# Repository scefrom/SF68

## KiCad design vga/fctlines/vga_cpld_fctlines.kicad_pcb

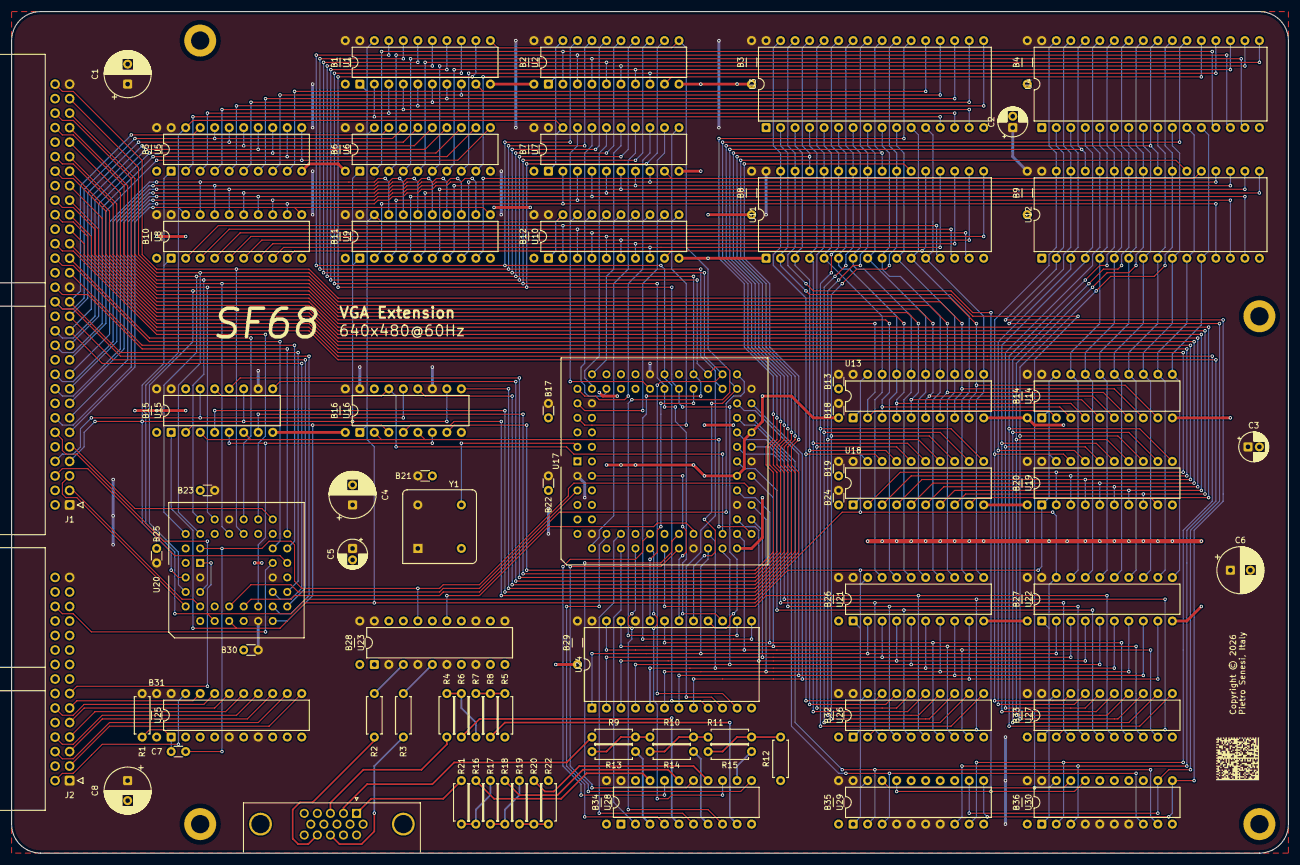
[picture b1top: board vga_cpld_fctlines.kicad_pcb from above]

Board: 2 copper layers, 223.5 x 147.3 mm, 104 parts (0 on the bottom side), 214 nets.

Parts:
B1, B2, B3, B4, B5, B6, B7, B8, B9, B10, B11, B12, B14, B15, B16, B20, B26, B27, B28, B29, B31, B32, B33, B34, B35, B36: 100n; C_Disc_D3.0mm_W1.6mm_P7.62mm
B13, B17, B18, B19, B21, B22, B23, B24, B25, B30: 100n; C_Disc_D3.0mm_W1.6mm_P2.54mm
C1, C4, C6, C8: 100u; CP_Radial_D8.0mm_P3.50mm
C2, C3, C5: 10u; CP_Radial_D5.0mm_P2.00mm
C7: 22p; C_Disc_D3.0mm_W1.6mm_P2.54mm
J1: perslota; IDC-Header_2x30_P2.54mm_Horizontal
J2: perslotb; IDC-Header_2x15_P2.54mm_Horizontal
J3: vga_connector; DSUB-15-HD_Socket_Horizontal_P2.29x1.90mm_EdgePinOffset3.03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
M1, M2, M3, M4: MountingHole_3.2mm_M3_DIN965_Pad
R1: 4.7k; R_Axial_DIN0207_L6.3mm_D2.5mm_P7.62mm_Horizontal
R2, R3: 75; R_Axial_DIN0207_L6.3mm_D2.5mm_P7.62mm_Horizontal
R4: 226; R_Axial_DIN0207_L6.3mm_D2.5mm_P7.62mm_Horizontal
R5, R6, R8, R12, R13, R14, R15, R16, R18, R20, R22: 200; R_Axial_DIN0207_L6.3mm_D2.5mm_P7.62mm_Horizontal
R7, R10, R11, R17, R19: 100; R_Axial_DIN0207_L6.3mm_D2.5mm_P7.62mm_Horizontal
R9, R21: 294; R_Axial_DIN0207_L6.3mm_D2.5mm_P7.62mm_Horizontal
U1, U2, U7, U10, U13, U14, U18, U19, U21, U22, U26, U27, U29, U30: 74AHC541; DIP-20_W7.62mm
U3, U4, U11, U12: AS6C4008-55PCN; DIP-32_W15.24mm
U5, U6, U8, U9: 74HC245; DIP-20_W7.62mm
U15, U16: 74HC157; DIP-16_W7.62mm
U17: ATF1508AS-xJx84; PLCC-84_THT-Socket
U20: ATF1502AS-xJx44; PLCC-44_THT-Socket
U23, U28: CY74FCT244; DIP-20_W7.62mm
U24: AT28C16; DIP-24_W15.24mm
U25: 74HC541; DIP-20_W7.62mm
Y1: CXO_DIP8_25.175MHz; Oscillator_DIP-8

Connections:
+5V: B1.1, B2.1, B3.1, B4.1, B5.1, B6.1, B7.1, B8.1, B9.1, B10.1, B11.1, B12.1, B13.1, B14.1, B15.1, B16.1, B17.1, B18.1, B19.1, B20.1, B21.1, B22.1, B23.1, B24.1, B25.1, B26.1, B27.1, B28.1, B29.1, B30.1, B31.1, B32.1, B33.1, B34.1, B35.1, B36.1, C1.1, C2.1, C3.1, C4.1, C5.1, C6.1, C8.1, J1.1, J1.31, J1.59, J2.1, J2.29, R1.1, U1.20 (VCC), U2.20 (VCC), U3.32 (VCC), U4.32 (VCC), U5.20 (VCC), U6.20 (VCC), U7.20 (VCC), U8.20 (VCC), U9.20 (VCC), U10.20 (VCC), U11.32 (VCC), U12.32 (VCC), U13.20 (VCC), U14.20 (VCC), U15.10 (I1c), U15.16 (VCC), U16.11 (I0c), U16.16 (VCC), U17.3 (VCC_INT), U17.13 (VCC_IO), U17.26 (VCC_IO), U17.38 (VCC_IO), U17.43 (VCC_INT), U17.53 (VCC_IO), U17.66 (VCC_IO), U17.78 (VCC_IO), U18.20 (VCC), U19.20 (VCC), U20.3 (VCC), U20.15 (VCC), U20.23 (VCC), U20.35 (VCC), U21.20 (VCC), U22.20 (VCC), U23.2, U23.4, U23.6, U23.8, U23.11, U23.13, U23.20 (VCC), U24.21 (~WE), U24.24 (VCC), U25.5 (A3), U25.7 (A5), U25.20 (VCC), U26.20 (VCC), U27.20 (VCC), U28.20 (VCC), U29.4 (A2), U29.5 (A3), U29.6 (A4), U29.7 (A5), U29.20 (VCC), U30.4 (A2), U30.5 (A3), U30.6 (A4), U30.7 (A5), U30.20 (VCC), Y1.1 (EN), Y1.8 (Vcc)
/AC.~P: J2.26, U20.25 (I/O/PD2)
/ADR_{0}: U17.51 (I/O), U21.9 (A7), U22.9 (A7), U24.8 (A0)
/ADR_{1}: U17.52 (I/O), U21.8 (A6), U22.8 (A6), U24.7 (A1)
/ADR_{2}: U17.37 (I/O), U21.7 (A5), U22.7 (A5), U24.6 (A2)
/ADR_{3}: U17.29 (I/O), U21.6 (A4), U22.6 (A4), U24.5 (A3)
/ADR_{4}: U17.30 (I/O), U21.5 (A3), U22.5 (A3), U24.4 (A4)
/ADR_{5}: U17.36 (I/O), U21.4 (A2), U22.4 (A2), U24.3 (A5)
/ADR_{6}: U17.35 (I/O), U21.3 (A1), U22.3 (A1), U24.2 (A6)
/ADR_{7}: U17.28 (I/O), U21.2 (A0), U22.2 (A0), U24.1 (A7)
/ADR_{8}: U17.34 (I/O), U24.23 (A8), U26.9 (A7), U27.9 (A7)
/ADR_{9}: U17.41 (I/O), U24.22 (A9), U26.8 (A6), U27.8 (A6)
/ADR_{10}: U17.40 (I/O), U24.19 (A10), U26.7 (A5), U27.7 (A5)
/ADR_{11}: U17.22 (I/O), U26.6 (A4), U27.6 (A4)
/ADR_{12}: U17.44 (I/O), U26.5 (A3), U27.5 (A3)
/ADR_{13}: U17.48 (I/O), U26.4 (A2), U27.4 (A2)
/ADR_{14}: U17.46 (I/O), U26.3 (A1), U27.3 (A1)
/ADR_{15}: U17.45 (I/O/PD2), U26.2 (A0), U27.2 (A0)
/ADR_{16}: U17.49 (I/O), U29.2 (A0), U30.9 (A7)
/ADR_{17}: U17.50 (I/O), U29.3 (A1), U30.8 (A6)
/A_{1}: J1.60, U13.9 (A7), U14.9 (A7), U20.34 (I/O)
/A_{2}: J1.57, U13.8 (A6), U14.8 (A6), U20.41 (I/O/GCLK3)
/A_{3}: J1.55, U13.7 (A5), U14.7 (A5), U20.40 (I/O)
/A_{4}: J1.56, U13.6 (A4), U14.6 (A4), U20.39 (I/O)
/A_{5}: J1.53, U13.5 (A3), U14.5 (A3), U20.36 (I/O)
/A_{6}: J1.54, U13.4 (A2), U14.4 (A2), U20.37 (I/O)
/A_{7}: J1.51, U13.3 (A1), U14.3 (A1), U20.4 (I/O)
/A_{8}: J1.49, U13.2 (A0), U14.2 (A0)
/A_{9}: J1.50, U18.9 (A7), U19.9 (A7)
/A_{10}: J1.47, U18.8 (A6), U19.8 (A6)
/A_{11}: J1.48, U18.7 (A5), U19.7 (A5)
/A_{12}: J1.45, U18.6 (A4), U19.6 (A4)
/A_{13}: J1.43, U18.5 (A3), U19.5 (A3)
/A_{14}: J1.44, U18.4 (A2), U19.4 (A2)
/A_{15}: J1.41, U18.3 (A1), U19.3 (A1)
/A_{16}: J1.42, U18.2 (A0), U19.2 (A0)
/A_{17}: J1.39, U29.9 (A7), U30.2 (A0)
/A_{18}: J1.37, U29.8 (A6), U30.3 (A1)
/A_{19}: J1.38, U20.31 (I/O)
/A_{20}: J1.35, U20.33 (I/O)
/A_{21}: J1.36, U20.27 (I/O)
/A_{22}: J1.33, U20.26 (I/O)
/A_{23}: J1.32, U20.28 (I/O)
/BE.~IO: J1.12, U20.5 (I/O)
/BE.~M: J1.9, U20.29 (I/O)
/CLK: U17.83 (I/GCLK1), Y1.5 (OUT)
/CM: U17.5 (I/O), U20.12 (I/O)
/DAT_{0}: U1.18 (Y0), U2.18 (Y0), U17.64 (I/O), U24.9 (D0)
/DAT_{1}: U1.17 (Y1), U2.17 (Y1), U17.57 (I/O), U24.10 (D1)
/DAT_{2}: U1.16 (Y2), U2.16 (Y2), U17.56 (I/O), U24.11 (D2)
/DAT_{3}: U1.15 (Y3), U2.15 (Y3), U17.60 (I/O), U24.13 (D3)
/DAT_{4}: U1.14 (Y4), U2.14 (Y4), U17.58 (I/O), U24.14 (D4)
/DAT_{5}: U1.13 (Y5), U2.13 (Y5), U17.65 (I/O), U24.15 (D5)
/DAT_{6}: U1.12 (Y6), U2.12 (Y6), U17.63 (I/O), U24.16 (D6)
/DAT_{7}: U1.11 (Y7), U2.11 (Y7), U17.55 (I/O), U24.17 (D7)
/DAT_{8}: U7.18 (Y0), U10.18 (Y0), U17.67 (I/O)
/DAT_{9}: U7.17 (Y1), U10.17 (Y1), U17.73 (I/O)
/DAT_{10}: U7.16 (Y2), U10.16 (Y2), U17.76 (I/O)
/DAT_{11}: U7.15 (Y3), U10.15 (Y3), U17.74 (I/O)
/DAT_{12}: U7.14 (Y4), U10.14 (Y4), U17.12 (I/O/PD1)
/DAT_{13}: U7.13 (Y5), U10.13 (Y5), U17.75 (I/O)
/DAT_{14}: U7.12 (Y6), U10.12 (Y6), U17.77 (I/O)
/DAT_{15}: U7.11 (Y7), U10.11 (Y7), U17.79 (I/O)
/DIR.~R: J1.8, U15.14 (I0d), U16.13 (I1d)
/DIR.~W: J1.7, U5.1 (A->B), U6.1 (A->B), U8.1 (A->B), U9.1 (A->B), U15.11 (I0c), U16.10 (I1c), U20.2 (I/GCLK2/OE2)
/DS.~L: J1.6, U20.24 (I/O)
/DS.~U: J1.5, U20.6 (I/O)
/D_{0}: J1.29, U5.18 (B0), U6.18 (B0), U20.20 (I/O)
/D_{1}: J1.30, U5.17 (B1), U6.17 (B1), U20.19 (I/O)
/D_{2}: J1.27, U5.16 (B2), U6.16 (B2), U20.18 (I/O)
/D_{3}: J1.25, U5.15 (B3), U6.15 (B3), U20.21 (I/O)
/D_{4}: J1.26, U5.14 (B4), U6.14 (B4)
/D_{5}: J1.23, U5.13 (B5), U6.13 (B5)
/D_{6}: J1.24, U5.12 (B6), U6.12 (B6)
/D_{7}: J1.21, U5.11 (B7), U6.11 (B7)
/D_{8}: J1.19, U8.18 (B0), U9.18 (B0)
/D_{9}: J1.20, U8.17 (B1), U9.17 (B1)
/D_{10}: J1.17, U8.16 (B2), U9.16 (B2)
/D_{11}: J1.18, U8.15 (B3), U9.15 (B3)
/D_{12}: J1.15, U8.14 (B4), U9.14 (B4)
/D_{13}: J1.13, U8.13 (B5), U9.13 (B5)
/D_{14}: J1.14, U8.12 (B6), U9.12 (B6)
/D_{15}: J1.11, U8.11 (B7), U9.11 (B7)
/IBSY: J2.2, U25.19 (G2)
/IRQ_{0}: J2.11, U25.18 (Y0)
/IRQ_{1}: J2.12, U25.17 (Y1)
/IRQ_{2}: J2.9, U25.16 (Y2)
/IRQ_{3}: J2.7, U25.15 (Y3)
/IRQ_{4}: J2.8, U25.14 (Y4)
/IRQ_{5}: J2.5, U25.13 (Y5)
/IRQ_{6}: J2.6, U25.12 (Y6)
/IRQ_{7}: J2.3, U25.11 (Y7)
/RGB_{0}: U17.25 (I/O), U28.15
/RGB_{1}: U17.24 (I/O), U28.11
/RGB_{2}: U17.21 (I/O), U28.17
/RGB_{3}: U17.20 (I/O/PD), U28.13
/RGB_{4}: U17.18 (I/O), U28.8
/RGB_{5}: U17.16 (I/O), U28.2
/RGB_{6}: U17.15 (I/O), U28.4
/RGB_{7}: U17.17 (I/O), U28.6
/UP: U17.54 (I/O), U20.14 (I/O)
/VBS: U1.1 (G1), U1.19 (G2), U6.19 (CE), U9.19 (CE), U10.1 (G1), U10.19 (G2), U14.1 (G1), U14.19 (G2), U15.1 (S), U16.1 (S), U19.1 (G1), U19.19 (G2), U20.11 (I/O/PD1), U21.1 (G1), U21.19 (G2), U26.1 (G1), U26.19 (G2), U29.1 (G1), U29.19 (G2)
/VB_{0}A_{0}: U3.12 (A0), U11.12 (A0), U13.11 (Y7), U21.11 (Y7)
/VB_{0}A_{1}: U3.11 (A1), U11.11 (A1), U13.12 (Y6), U21.12 (Y6)
/VB_{0}A_{2}: U3.10 (A2), U11.10 (A2), U13.13 (Y5), U21.13 (Y5)
/VB_{0}A_{3}: U3.9 (A3), U11.9 (A3), U13.14 (Y4), U21.14 (Y4)
/VB_{0}A_{4}: U3.8 (A4), U11.8 (A4), U13.15 (Y3), U21.15 (Y3)
/VB_{0}A_{5}: U3.7 (A5), U11.7 (A5), U13.16 (Y2), U21.16 (Y2)
/VB_{0}A_{6}: U3.6 (A6), U11.6 (A6), U13.17 (Y1), U21.17 (Y1)
/VB_{0}A_{7}: U3.5 (A7), U11.5 (A7), U13.18 (Y0), U21.18 (Y0)
/VB_{0}A_{8}: U3.27 (A8), U11.27 (A8), U18.11 (Y7), U26.11 (Y7)
/VB_{0}A_{9}: U3.26 (A9), U11.26 (A9), U18.12 (Y6), U26.12 (Y6)
/VB_{0}A_{10}: U3.23 (A10), U11.23 (A10), U18.13 (Y5), U26.13 (Y5)
/VB_{0}A_{11}: U3.25 (A11), U11.25 (A11), U18.14 (Y4), U26.14 (Y4)
/VB_{0}A_{12}: U3.4 (A12), U11.4 (A12), U18.15 (Y3), U26.15 (Y3)
/VB_{0}A_{13}: U3.28 (A13), U11.28 (A13), U18.16 (Y2), U26.16 (Y2)
/VB_{0}A_{14}: U3.3 (A14), U11.3 (A14), U18.17 (Y1), U26.17 (Y1)
/VB_{0}A_{15}: U3.31 (A15), U11.31 (A15), U18.18 (Y0), U26.18 (Y0)
/VB_{0}A_{16}: U3.2 (A16), U11.2 (A16), U29.18 (Y0), U30.18 (Y0)
/VB_{0}A_{17}: U3.30 (A17), U11.30 (A17), U29.17 (Y1), U30.17 (Y1)
/VB_{0}C.~E_{L}: U3.22 (CE#), U16.7 (Zb)
/VB_{0}C.~E_{U}: U11.22 (CE#), U16.4 (Za)
/VB_{0}C.~R: U3.24 (OE#), U11.24 (OE#), U16.12 (Zd)
/VB_{0}C.~W: U3.29 (WE#), U11.29 (WE#), U16.9 (Zc)
/VB_{0}D_{0}: U1.2 (A0), U3.13 (DQ0), U5.2 (A0)
/VB_{0}D_{1}: U1.3 (A1), U3.14 (DQ1), U5.3 (A1)
/VB_{0}D_{2}: U1.4 (A2), U3.15 (DQ2), U5.4 (A2)
/VB_{0}D_{3}: U1.5 (A3), U3.17 (DQ3), U5.5 (A3)
/VB_{0}D_{4}: U1.6 (A4), U3.18 (DQ4), U5.6 (A4)
/VB_{0}D_{5}: U1.7 (A5), U3.19 (DQ5), U5.7 (A5)
/VB_{0}D_{6}: U1.8 (A6), U3.20 (DQ6), U5.8 (A6)
/VB_{0}D_{7}: U1.9 (A7), U3.21 (DQ7), U5.9 (A7)
/VB_{0}D_{8}: U8.2 (A0), U10.2 (A0), U11.13 (DQ0)
/VB_{0}D_{9}: U8.3 (A1), U10.3 (A1), U11.14 (DQ1)
/VB_{0}D_{10}: U8.4 (A2), U10.4 (A2), U11.15 (DQ2)
/VB_{0}D_{11}: U8.5 (A3), U10.5 (A3), U11.17 (DQ3)
/VB_{0}D_{12}: U8.6 (A4), U10.6 (A4), U11.18 (DQ4)
/VB_{0}D_{13}: U8.7 (A5), U10.7 (A5), U11.19 (DQ5)
/VB_{0}D_{14}: U8.8 (A6), U10.8 (A6), U11.20 (DQ6)
/VB_{0}D_{15}: U8.9 (A7), U10.9 (A7), U11.21 (DQ7)
/VB_{1}A_{0}: U4.12 (A0), U12.12 (A0), U14.11 (Y7), U22.11 (Y7)
/VB_{1}A_{1}: U4.11 (A1), U12.11 (A1), U14.12 (Y6), U22.12 (Y6)
/VB_{1}A_{2}: U4.10 (A2), U12.10 (A2), U14.13 (Y5), U22.13 (Y5)
/VB_{1}A_{3}: U4.9 (A3), U12.9 (A3), U14.14 (Y4), U22.14 (Y4)
/VB_{1}A_{4}: U4.8 (A4), U12.8 (A4), U14.15 (Y3), U22.15 (Y3)
/VB_{1}A_{5}: U4.7 (A5), U12.7 (A5), U14.16 (Y2), U22.16 (Y2)
/VB_{1}A_{6}: U4.6 (A6), U12.6 (A6), U14.17 (Y1), U22.17 (Y1)
/VB_{1}A_{7}: U4.5 (A7), U12.5 (A7), U14.18 (Y0), U22.18 (Y0)
/VB_{1}A_{8}: U4.27 (A8), U12.27 (A8), U19.11 (Y7), U27.11 (Y7)
/VB_{1}A_{9}: U4.26 (A9), U12.26 (A9), U19.12 (Y6), U27.12 (Y6)
/VB_{1}A_{10}: U4.23 (A10), U12.23 (A10), U19.13 (Y5), U27.13 (Y5)
/VB_{1}A_{11}: U4.25 (A11), U12.25 (A11), U19.14 (Y4), U27.14 (Y4)
/VB_{1}A_{12}: U4.4 (A12), U12.4 (A12), U19.15 (Y3), U27.15 (Y3)
/VB_{1}A_{13}: U4.28 (A13), U12.28 (A13), U19.16 (Y2), U27.16 (Y2)
/VB_{1}A_{14}: U4.3 (A14), U12.3 (A14), U19.17 (Y1), U27.17 (Y1)
/VB_{1}A_{15}: U4.31 (A15), U12.31 (A15), U19.18 (Y0), U27.18 (Y0)
/VB_{1}A_{16}: U4.2 (A16), U12.2 (A16), U29.11 (Y7), U30.11 (Y7)
/VB_{1}A_{17}: U4.30 (A17), U12.30 (A17), U29.12 (Y6), U30.12 (Y6)
/VB_{1}C.~E_{L}: U4.22 (CE#), U15.7 (Zb)
/VB_{1}C.~E_{U}: U12.22 (CE#), U15.4 (Za)
/VB_{1}C.~R: U4.24 (OE#), U12.24 (OE#), U15.12 (Zd)
/VB_{1}C.~W: U4.29 (WE#), U12.29 (WE#), U15.9 (Zc)
/VB_{1}D_{0}: U2.2 (A0), U4.13 (DQ0), U6.2 (A0)
/VB_{1}D_{1}: U2.3 (A1), U4.14 (DQ1), U6.3 (A1)
/VB_{1}D_{2}: U2.4 (A2), U4.15 (DQ2), U6.4 (A2)
/VB_{1}D_{3}: U2.5 (A3), U4.17 (DQ3), U6.5 (A3)
/VB_{1}D_{4}: U2.6 (A4), U4.18 (DQ4), U6.6 (A4)
/VB_{1}D_{5}: U2.7 (A5), U4.19 (DQ5), U6.7 (A5)
/VB_{1}D_{6}: U2.8 (A6), U4.20 (DQ6), U6.8 (A6)
/VB_{1}D_{7}: U2.9 (A7), U4.21 (DQ7), U6.9 (A7)
/VB_{1}D_{8}: U7.2 (A0), U9.2 (A0), U12.13 (DQ0)
/VB_{1}D_{9}: U7.3 (A1), U9.3 (A1), U12.14 (DQ1)
/VB_{1}D_{10}: U7.4 (A2), U9.4 (A2), U12.15 (DQ2)
/VB_{1}D_{11}: U7.5 (A3), U9.5 (A3), U12.17 (DQ3)
/VB_{1}D_{12}: U7.6 (A4), U9.6 (A4), U12.18 (DQ4)
/VB_{1}D_{13}: U7.7 (A5), U9.7 (A5), U12.19 (DQ5)
/VB_{1}D_{14}: U7.8 (A6), U9.8 (A6), U12.20 (DQ6)
/VB_{1}D_{15}: U7.9 (A7), U9.9 (A7), U12.21 (DQ7)
/vga_interface/BLUE: J3.3, R4.2
/vga_interface/GREEN: J3.2, R9.2
/vga_interface/RED: J3.1, R21.2
/vga_interface/~HSYNC: J3.13, R3.2
/vga_interface/~VSYNC: J3.14, R2.2
/~BE_{L}: U15.5 (I0b), U16.6 (I1b), U20.16 (I/O)
/~BE_{U}: U15.2 (I0a), U16.3 (I1a), U20.17 (I/O)
/~CME: U17.4 (I/O), U24.18 (~CE)
/~CMO: U17.61 (I/O), U24.20 (~OE)
/~HS: U17.27 (I/O), U23.15
/~RES: J2.13, U20.1 (I/GCLR)
/~RIH: J1.3, U20.8 (I/O)
/~VBS: U2.1 (G1), U2.19 (G2), U5.19 (CE), U7.1 (G1), U7.19 (G2), U8.19 (CE), U13.1 (G1), U13.19 (G2), U18.1 (G1), U18.19 (G2), U20.9 (I/O), U22.1 (G1), U22.19 (G2), U27.1 (G1), U27.19 (G2), U30.1 (G1), U30.19 (G2)
/~VME: U15.3 (I1a), U15.6 (I1b), U16.2 (I0a), U16.5 (I0b), U17.33 (I/O)
/~VMO: U15.13 (I1d), U16.14 (I0d), U17.31 (I/O)
/~VS: C7.2, U17.39 (I/O), U20.43 (I/GCLK1), U23.17
GND: B1.2, B2.2, B3.2, B4.2, B5.2, B6.2, B7.2, B8.2, B9.2, B10.2, B11.2, B12.2, B13.2, B14.2, B15.2, B16.2, B17.2, B18.2, B19.2, B20.2, B21.2, B22.2, B23.2, B24.2, B25.2, B26.2, B27.2, B28.2, B29.2, B30.2, B31.2, B32.2, B33.2, B34.2, B35.2, B36.2, C1.2, C2.2, C3.2, C4.2, C5.2, C6.2, C8.2, J1.4, J1.10, J1.16, J1.22, J1.28, J1.34, J1.40, J1.46, J1.52, J1.58, J2.4, J2.10, J2.16, J2.21, J2.22, J2.28, J3.0, J3.5, J3.6, J3.7, J3.8, J3.10, M1.1, M2.1, M3.1, M4.1, R5.2, R12.2, R22.2, U1.10 (GND), U2.10 (GND), U3.1 (A18), U3.16 (VSS), U4.1 (A18), U4.16 (VSS), U5.10 (GND), U6.10 (GND), U7.10 (GND), U8.10 (GND), U9.10 (GND), U10.10 (GND), U11.1 (A18), U11.16 (VSS), U12.1 (A18), U12.16 (VSS), U13.10 (GND), U14.10 (GND), U15.8 (GND), U15.15 (E), U16.8 (GND), U16.15 (E), U17.7 (GND), U17.19 (GND), U17.32 (GND), U17.42 (GND), U17.47 (GND), U17.59 (GND), U17.72 (GND), U17.82 (GND), U18.10 (GND), U19.10 (GND), U20.10 (GND), U20.22 (GND), U20.30 (GND), U20.42 (GND), U21.10 (GND), U22.10 (GND), U23.1, U23.10 (GND), U23.19, U24.12 (GND), U25.2 (A0), U25.3 (A1), U25.4 (A2), U25.6 (A4), U25.8 (A6), U25.9 (A7), U25.10 (GND), U26.10 (GND), U27.10 (GND), U28.1, U28.10 (GND), U28.19, U29.10 (GND), U30.10 (GND), Y1.4 (GND)
unnamed: R2.1, U23.3
unnamed: R3.1, U23.5
unnamed: R4.1, R6.2, R7.1
unnamed: R5.1, R7.2, R8.2
unnamed: R6.1, U28.5
unnamed: R8.1, U28.9
unnamed: R9.1, R10.1, R13.2
unnamed: R10.2, R11.1, R14.2
unnamed: R11.2, R12.1, R15.2
unnamed: R13.1, U28.3
unnamed: R14.1, U28.7
unnamed: R15.1, U28.12
unnamed: R16.1, U28.18
unnamed: R16.2, R17.1, R21.1
unnamed: R17.2, R18.2, R19.1
unnamed: R18.1, U28.16
unnamed: R19.2, R20.2, R22.1
unnamed: R20.1, U28.14
unnamed: C7.1, R1.2, U25.1 (G1)

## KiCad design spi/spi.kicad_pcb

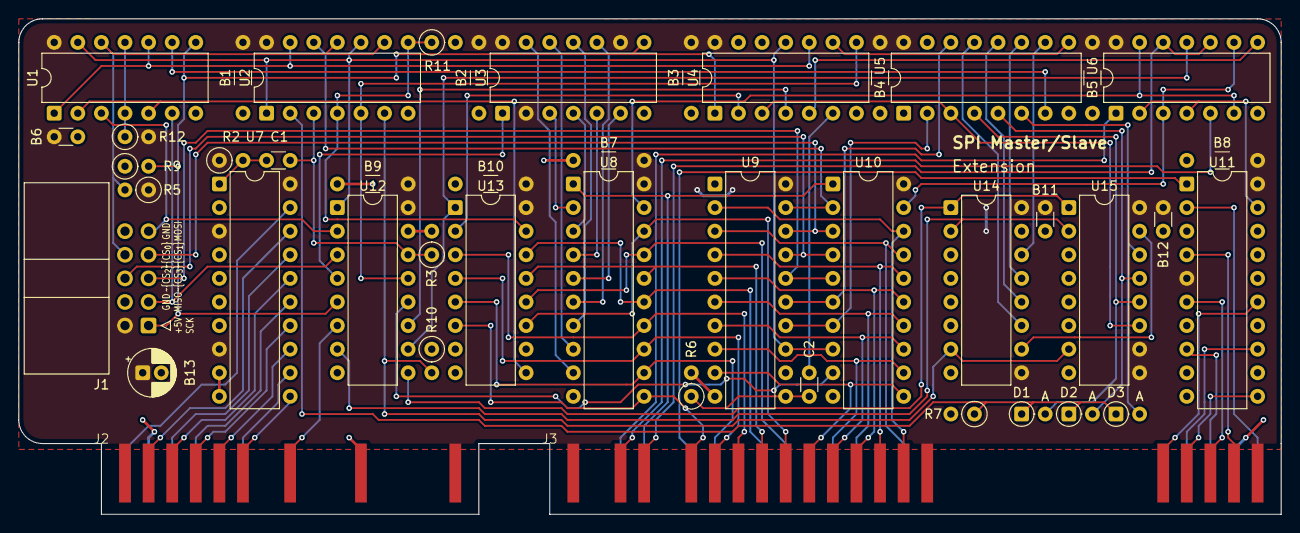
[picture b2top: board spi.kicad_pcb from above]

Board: 2 copper layers, 135.9 x 53.3 mm, 45 parts (0 on the bottom side), 92 nets.

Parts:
B1, B2, B3, B4, B5, B7, B8, B9, B10: 100n; C_Disc_D3.0mm_W1.6mm_P7.62mm
B6, B11, B12: 100n; C_Disc_D3.0mm_W1.6mm_P2.54mm
B13: 10u; CP_Radial_D5.0mm_P2.00mm
C1, C2: 22pF; C_Disc_D3.0mm_W1.6mm_P2.54mm
D1, D2, D3: D_Schottky_Filled; D_DO-35_SOD27_P2.54mm_Vertical_AnodeUp
J1: spi-port; IDC-Header_2x05_P2.54mm_Horizontal
J2: perslot1b; edge_connector_15p_2.54mm
J3: perslot1a; edge_connector_30p_2.54mm
R2, R6: 1k; R_Axial_DIN0207_L6.3mm_D2.5mm_P2.54mm_Vertical
R3, R10, R11, R12: 10k; R_Axial_DIN0207_L6.3mm_D2.5mm_P2.54mm_Vertical
R5, R9: 4k7; R_Axial_DIN0207_L6.3mm_D2.5mm_P2.54mm_Vertical
R7: 2k; R_Axial_DIN0207_L6.3mm_D2.5mm_P2.54mm_Vertical
U1, U2: 74HC125; DIP-14_W7.62mm
U3: 74HC164; DIP-14_W7.62mm
U4: 74HC04; DIP-14_W7.62mm
U5: 74HC153; DIP-16_W7.62mm
U6: 74HC32; DIP-14_W7.62mm
U7, U8, U10: 74HC541; DIP-20_W7.62mm
U9: 74HC573; DIP-20_W7.62mm
U11: 74HC688; DIP-20_W7.62mm
U12: 74HC157; DIP-16_W7.62mm
U13: 74HC165; DIP-16_W7.62mm
U14, U15: 74HC161; DIP-16_W7.62mm

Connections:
+5V: B1.1, B2.1, B3.1, B4.1, B5.1, B6.1, B7.1, B8.1, B9.1, B10.1, B11.1, B12.1, B13.1, J1.2, J2.1, J2.29, J3.1, J3.31, J3.59, R2.1, R5.1, R12.2, U1.14 (VCC), U2.14 (VCC), U3.2 (DSB), U3.9 (~MR), U3.14 (VCC), U4.14 (VCC), U5.16 (VCC), U6.14 (VCC), U7.3 (A1), U7.8 (A6), U7.20 (VCC), U8.20 (VCC), U9.20 (VCC), U10.20 (VCC), U11.5 (R1), U11.20 (VCC), U12.16 (VCC), U13.16 (VCC), U14.9 (~PE), U14.16 (VCC), U15.9 (~PE), U15.10 (CET), U15.16 (VCC)
/A_{1}: J3.60, U11.2 (P0)
/A_{2}: J3.57, U11.4 (P1)
/A_{3}: J3.55, U11.6 (P2)
/A_{4}: J3.56, U11.8 (P3)
/A_{5}: J3.53, U11.11 (P4)
/A_{6}: J3.54, U11.13 (P5)
/A_{7}: J3.51, U11.15 (P6)
/CCK: U12.7 (Zb), U14.2 (CP), U15.2 (CP)
/CEN: R10.2, U2.6, U14.7 (CEP), U15.7 (CEP)
/CLK: J2.15, U12.6 (I1b)
/D_{0}: J3.29, U9.2 (D0), U10.18 (Y0)
/D_{1}: J3.30, U9.3 (D1), U10.17 (Y1)
/D_{2}: J3.27, U9.4 (D2), U10.16 (Y2)
/D_{3}: J3.25, U9.5 (D3), U10.15 (Y3)
/D_{4}: J3.26, U9.6 (D4), U10.14 (Y4)
/D_{5}: J3.23, U9.7 (D5), U10.13 (Y5)
/D_{6}: J3.24, U9.8 (D6), U10.12 (Y6)
/D_{7}: J3.21, U9.9 (D7), U10.11 (Y7)
/D_{8}: J3.19, U8.18 (Y0), U13.11 (D0)
/D_{9}: J3.20, U8.17 (Y1), U13.12 (D1)
/D_{10}: J3.17, U8.16 (Y2), U13.13 (D2)
/D_{11}: J3.18, U8.15 (Y3), U13.14 (D3)
/D_{12}: J3.15, U8.14 (Y4), U13.3 (D4)
/D_{13}: J3.13, U8.13 (Y5), U13.4 (D5)
/D_{14}: J3.14, U8.12 (Y6), U13.5 (D6)
/D_{15}: J3.11, U8.11 (Y7), U13.6 (D7)
/FQ_{0}: U5.14 (S0), U9.15 (Q4), U10.6 (A4)
/FQ_{1}: U5.2 (S1), U9.14 (Q5), U10.7 (A5)
/IBSY: J2.2, U7.19 (G2)
/IRQ_{0}: J2.11, U7.11 (Y7)
/IRQ_{1}: J2.12, U7.12 (Y6)
/IRQ_{2}: J2.9, U7.13 (Y5)
/IRQ_{3}: J2.7, U7.14 (Y4)
/IRQ_{4}: J2.8, U7.15 (Y3)
/IRQ_{5}: J2.5, U7.16 (Y2)
/IRQ_{6}: J2.6, U7.17 (Y1)
/IRQ_{7}: J2.3, U7.18 (Y0)
/MISO: J1.3, U1.6, U12.3 (I1a)
/MOSI: J1.9, U1.3, U12.2 (I0a)
/MST: U1.13, U2.1, U2.10, U4.11, U9.13 (Q6), U10.8 (A6), U12.1 (S)
/SCK: J1.1, R9.2, U1.8, U3.8 (CP), U4.1, U12.5 (I0b)
/SCK_{f0}: D3.2 (A), U5.6 (I0a), U15.14 (Q0)
/SCK_{f1}: D2.2 (A), U5.5 (I1a), U15.13 (Q1)
/SCK_{f2}: D1.2 (A), U5.4 (I2a), U15.12 (Q2)
/SCK_{f3}: U4.3, U5.3 (I3a), U15.11 (Q3)
/SIN: U3.1 (DSA), U12.4 (Za)
/SOUT: U1.2, U1.5, U13.9 (Q7)
/TRF: U10.9 (A7), U12.12 (Zd)
/TRF_{M}: U2.5, U4.8, U12.13 (I1d)
/TRF_{S}: C1.1, R3.1, U2.3, U12.14 (I0d)
/~CR: U12.9 (Zc), U14.1 (~MR), U15.1 (~MR)
/~CS_{0}: J1.8, R5.2, U1.12, U2.9, U2.11
/~CS_{1}: J1.7, U9.18 (Q1), U10.3 (A1)
/~CS_{2}: J1.6, U9.17 (Q2), U10.4 (A2)
/~CS_{3}: J1.5, U9.16 (Q3), U10.5 (A3)
/~DS: U6.6, U6.13, U8.19 (G2)
/~DW: U6.11, U12.10 (I1c), U13.1 (~PL)
/~FS: U6.3, U6.9, U10.19 (G2)
/~FW: U4.5, U6.8
/~IO: J3.12, U11.1 (G)
/~LS: J3.6, U6.1
/~MST: U1.1, U1.10, U2.13, U4.10
/~ON: R11.1, U2.4, U2.8, U13.15 (~CE)
/~RD: J3.8, U8.1 (G1), U10.1 (G1)
/~SCK: U4.2, U13.2 (CP)
/~S: U6.2, U6.4, U11.19 (P=R)
/~TRF_{f0}: U5.10 (I0b), U14.14 (Q0)
/~TRF_{f1}: U5.11 (I1b), U14.13 (Q1)
/~TRF_{f2}: U5.12 (I2b), U14.12 (Q2)
/~TRF_{f3}: U5.13 (I3b), U14.11 (Q3)
/~US: J3.5, U6.5
/~WR: J3.7, U6.10, U6.12
GND: B1.2, B2.2, B3.2, B4.2, B5.2, B6.2, B7.2, B8.2, B9.2, B10.2, B11.2, B12.2, B13.2, J1.4, J1.10, J2.4, J2.16, J2.21, J2.22, J2.28, J3.4, J3.22, J3.34, J3.40, J3.46, J3.52, J3.58, R3.2, R6.2, R7.2, R9.1, R10.1, R11.2, U1.7 (GND), U2.7 (GND), U3.7 (GND), U4.7 (GND), U4.13, U5.1 (Ea), U5.8 (GND), U5.15 (Eb), U6.7 (GND), U7.2 (A0), U7.4 (A2), U7.5 (A3), U7.6 (A4), U7.7 (A5), U7.9 (A7), U7.10 (GND), U8.10 (GND), U9.1 (OE), U9.10 (GND), U10.10 (GND), U11.3 (R0), U11.7 (R2), U11.9 (R3), U11.10 (GND), U11.12 (R4), U11.14 (R5), U11.16 (R6), U11.17 (P7), U11.18 (R7), U12.8 (GND), U12.15 (E), U13.8 (GND), U13.10 (DS), U14.3 (D0), U14.4 (D1), U14.5 (D2), U14.6 (D3), U14.8 (GND), U15.3 (D0), U15.4 (D1), U15.5 (D2), U15.6 (D3), U15.8 (GND)
unnamed: C2.1, U4.6
unnamed: D1.1 (K), D2.1 (K), D3.1 (K), R7.1, U2.2
unnamed: R12.1, U1.4, U1.11
unnamed: U3.3 (Q0), U8.2 (A0)
unnamed: U3.4 (Q1), U8.3 (A1)
unnamed: U3.5 (Q2), U8.4 (A2)
unnamed: U3.6 (Q3), U8.5 (A3)
unnamed: U3.10 (Q4), U8.6 (A4)
unnamed: U3.11 (Q5), U8.7 (A5)
unnamed: U3.12 (Q6), U8.8 (A6)
unnamed: U3.13 (Q7), U8.9 (A7)
unnamed: U1.9, U5.7 (Za)
unnamed: U4.9, U5.9 (Zb)
unnamed: C1.2, R2.2, U7.1 (G1)
unnamed: C2.2, R6.1, U9.11 (Load)
unnamed: U2.12, U9.19 (Q0), U10.2 (A0)
unnamed: U4.4, U12.11 (I0c)
unnamed: U14.10 (CET), U15.15 (TC)

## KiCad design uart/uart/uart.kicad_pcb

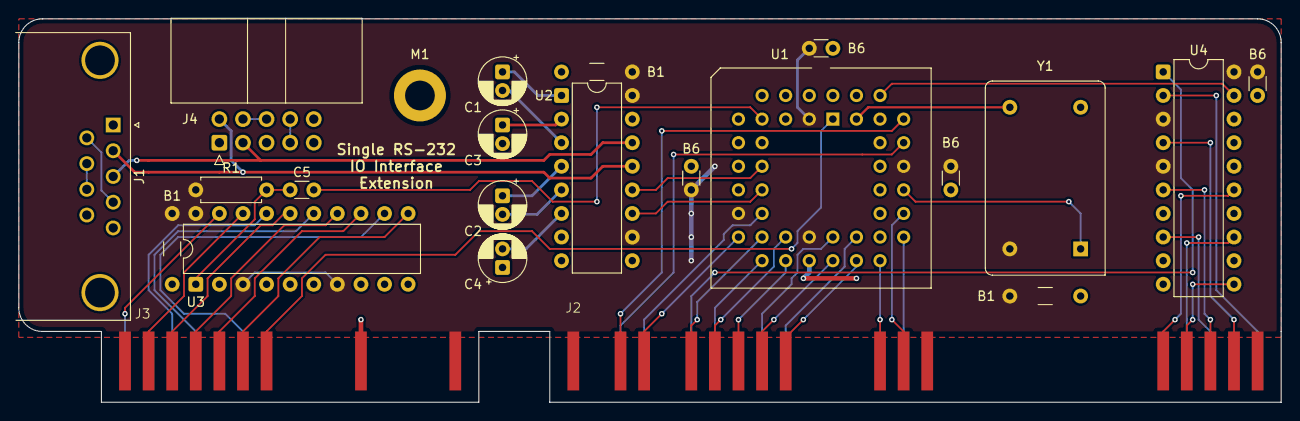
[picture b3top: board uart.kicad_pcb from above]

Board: 2 copper layers, 135.9 x 41.3 mm, 23 parts (0 on the bottom side), 54 nets.

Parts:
B1, B1#2, B1#3: 100n; C_Disc_D3.0mm_W1.6mm_P7.62mm
B6, B6#2, B6#3, B6#4: 100n; C_Disc_D3.0mm_W1.6mm_P2.54mm
C1, C2, C3, C4: 1u; CP_Radial_D5.0mm_P2.00mm
C5: 22p; C_Disc_D3.0mm_W1.6mm_P2.54mm
J1: DE9_Pins_MountingHoles; DSUB-9_Pins_Horizontal_P2.77x2.84mm_EdgePinOffset7.70mm_Hou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
J2: perslota; edge_connector_30p_2.54mm
J3: perslotb; edge_connector_15p_2.54mm
J4: Conn_02x05_Top_Bottom; IDC-Header_2x05_P2.54mm_Horizontal
M1: MountingHole_3.2mm_M3_DIN965_Pad
R1: 4k7; R_Axial_DIN0207_L6.3mm_D2.5mm_P7.62mm_Horizontal
U1: ATF1504AS-xJx44; PLCC-44_THT-Socket
U2: MAX232; DIP-16_W7.62mm
U3: 74HC541; DIP-20_W7.62mm
U4: 74HC688; DIP-20_W7.62mm
Y1: 1.8432MHz; Oscillator_DIP-14

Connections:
+5V: B1.1, B1#2.1, B1#3.1, B6.1, B6#2.1, B6#3.1, B6#4.1, J2.1, J2.31, J2.59, J3.1, J3.29, R1.1, U1.3 (VCC), U1.15 (VCC), U1.23 (VCC), U1.35 (VCC), U2.10 (T2IN), U2.16 (VCC), U3.3 (A1), U3.7 (A5), U3.20 (VCC), U4.3 (R0), U4.5 (R1), U4.20 (VCC), Y1.14 (Vcc)
/A_{1}: J2.60, U4.2 (P0)
/A_{2}: J2.57, U4.4 (P1)
/A_{3}: J2.55, U4.6 (P2)
/A_{4}: J2.56, U4.8 (P3)
/A_{5}: J2.53, U4.11 (P4)
/A_{6}: J2.54, U4.13 (P5)
/A_{7}: J2.51, U4.15 (P6)
/CLK: U1.43 (I/GCLK1), Y1.8 (OUT)
/D_{0}: J2.29, U1.31 (I/O)
/D_{1}: J2.30, U1.29 (I/O)
/D_{2}: J2.27, U1.28 (I/O)
/D_{8}: J2.19, U1.26 (I/O)
/D_{9}: J2.20, U1.27 (I/O)
/D_{10}: J2.17, U1.24 (I/O)
/D_{11}: J2.18, U1.25 (I/O/PD2)
/D_{12}: J2.15, U1.20 (I/O)
/D_{13}: J2.13, U1.21 (I/O)
/D_{14}: J2.14, U1.18 (I/O)
/D_{15}: J2.11, U1.19 (I/O)
/IBSY: J3.2, U3.19 (G2)
/IRQ: C5.1, U1.8 (I/O)
/IRQ_{0}: J3.11, U3.11 (Y7)
/IRQ_{1}: J3.12, U3.12 (Y6)
/IRQ_{2}: J3.9, U3.13 (Y5)
/IRQ_{3}: J3.7, U3.14 (Y4)
/IRQ_{4}: J3.8, U3.15 (Y3)
/IRQ_{5}: J3.5, U3.16 (Y2)
/IRQ_{6}: J3.6, U3.17 (Y1)
/IRQ_{7}: J3.3, U3.18 (Y0)
/ON: U1.33 (I/O), Y1.1 (EN)
/RX: U1.12 (I/O), U2.12 (R1OUT)
/RX_{RS232}: J1.2, J4.2, U2.13 (R1IN)
/TX: U1.14 (I/O), U2.11 (T1IN)
/TX_{RS232}: J1.3, J4.3, U2.14 (T1OUT)
/~CS: U1.40 (I/O), U4.19 (P=R)
/~IOS: J2.12, U4.1 (G)
/~LS: J2.6, U1.37 (I/O)
/~RES: J3.13, U1.1 (I/GCLR)
/~RE: J2.8, U1.16 (I/O)
/~US: J2.5, U1.39 (I/O)
/~WE: J2.7, U1.17 (I/O)
GND: B1.2, B1#2.2, B1#3.2, B6.2, B6#2.2, B6#3.2, B6#4.2, C3.2, C4.1, J1.0 (PAD), J1.5, J2.4, J2.22, J2.28, J2.34, J2.40, J2.46, J2.52, J3.4, J3.16, J3.21, J3.22, J3.28, J4.5, M1.1, U1.10 (GND), U1.22 (GND), U1.30 (GND), U1.42 (GND), U2.15 (GND), U3.2 (A0), U3.4 (A2), U3.5 (A3), U3.6 (A4), U3.8 (A6), U3.9 (A7), U3.10 (GND), U4.7 (R2), U4.9 (R3), U4.10 (GND), U4.12 (R4), U4.14 (R5), U4.16 (R6), U4.17 (P7), U4.18 (R7), Y1.7 (GND)
unnamed: J1.4, J1.6
unnamed: J1.7, J1.8
unnamed: J4.4, J4.6
unnamed: J4.7, J4.8
unnamed: C1.1, U2.1 (C1+)
unnamed: C1.2, U2.3 (C1-)
unnamed: C2.1, U2.4 (C2+)
unnamed: C2.2, U2.5 (C2-)
unnamed: C3.1, U2.2 (VS+)
unnamed: C4.2, U2.6 (VS-)
unnamed: C5.2, R1.2, U3.1 (G1)

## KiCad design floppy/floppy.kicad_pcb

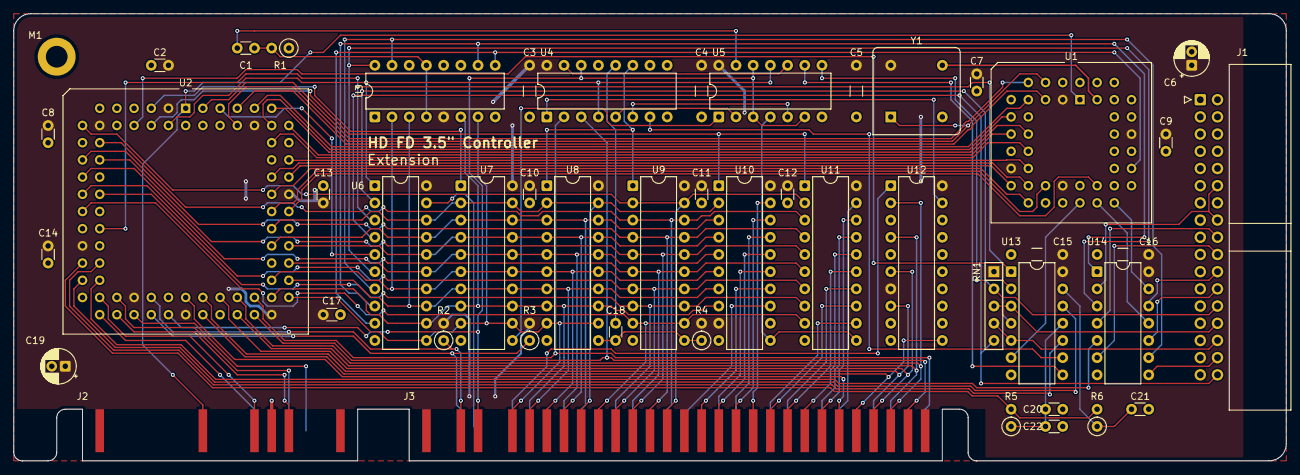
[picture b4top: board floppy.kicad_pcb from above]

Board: 2 copper layers, 188.0 x 66.0 mm, 48 parts (0 on the bottom side), 110 nets.

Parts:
C1, C18: 22p; C_Disc_D3.0mm_W1.6mm_P2.54mm
C2, C7, C8, C9, C10, C11, C12, C13, C14, C17, C20, C22: 100n; C_Disc_D3.0mm_W1.6mm_P2.54mm
C3, C4, C5, C15, C16: 100n; C_Disc_D3.0mm_W1.6mm_P7.62mm
C6, C19: 10u; CP_Radial_D5.0mm_P2.00mm
C21: 220p; C_Disc_D3.0mm_W1.6mm_P2.54mm
J1: driveint; IDC-Header_2x17_P2.54mm_Horizontal
J2: perslotb; edge_connector_15p_2.54mm
J3: perslota; edge_connector_30p_2.54mm
M1: MountingHole_3.2mm_M3_DIN965_Pad
R1, R4: 4k7; R_Axial_DIN0207_L6.3mm_D2.5mm_P2.54mm_Vertical
R2, R3, R5, R6: 10k; R_Axial_DIN0207_L6.3mm_D2.5mm_P2.54mm_Vertical
RN1: 1k; R_Array_SIP5
U1: SF2202; PLCC-44_THT-Socket
U2: SF2203; PLCC-84_THT-Socket
U3: 74HC75; DIP-16_W7.62mm
U4: 74HC139; DIP-16_W7.62mm
U5: 74HC02; DIP-14_W7.62mm
U6: 74HC541; DIP-20_W7.62mm
U7, U8, U9, U10, U11: 74HC574; DIP-20_W7.62mm
U12: 74HC688; DIP-20_W7.62mm
U13: 74HC14; DIP-14_W7.62mm
U14: 74HC05; DIP-14_W7.62mm
Y1: 16MHz; Oscillator_DIP-8

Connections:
+5V: C2.1, C3.1, C4.1, C5.1, C6.1, C7.1, C8.1, C9.1, C10.1, C11.1, C12.1, C13.1, C14.1, C15.1, C16.1, C17.1, C19.1, J2.1, J2.29, J3.1, J3.31, J3.59, R2.2, R3.2, R4.2, RN1.1 (R1), U1.3 (VCC), U1.15 (VCC), U1.23 (VCC), U1.35 (VCC), U2.3 (VCC), U2.13 (VCC), U2.26 (VCC), U2.38 (VCC), U2.43 (VCC), U2.53 (VCC), U2.66 (VCC), U2.78 (VCC), U3.5 (VCC), U4.16 (VCC), U5.14 (VCC), U6.20 (VCC), U7.20 (VCC), U8.20 (VCC), U9.20 (VCC), U10.9 (D7), U10.20 (VCC), U11.20 (VCC), U12.7 (R2), U12.20 (VCC), U13.14 (VCC), U14.14 (VCC), Y1.8 (Vcc)
/A1M: U1.18 (A1M), U2.67 (A1M)
/A_{1}: J3.60, U2.52 (A_{0}), U4.2 (A0)
/A_{2}: J3.57, U2.51 (A_{1}), U4.3 (A1)
/A_{3}: J3.55, U2.50 (A_{2}), U12.2 (P0)
/A_{4}: J3.56, U2.49 (A_{3}), U12.4 (P1)
/A_{5}: J3.53, U2.48 (A_{4}), U12.6 (P2)
/A_{6}: J3.54, U2.46 (A_{5}), U12.8 (P3)
/A_{7}: J3.51, U2.45 (A_{6}), U12.11 (P4)
/A_{8}: J3.49, U2.44 (A_{7})
/A_{9}: J3.50, U11.19 (Q0)
/A_{10}: J3.47, U11.18 (Q1)
/A_{11}: J3.48, U11.17 (Q2)
/A_{12}: J3.45, U11.16 (Q3)
/A_{13}: J3.43, U11.15 (Q4)
/A_{14}: J3.44, U11.14 (Q5)
/A_{15}: J3.41, U11.13 (Q6)
/A_{16}: J3.42, U11.12 (Q7)
/A_{17}: J3.39, U10.19 (Q0)
/A_{18}: J3.37, U10.18 (Q1)
/A_{19}: J3.38, U10.17 (Q2)
/A_{20}: J3.35, U10.16 (Q3)
/A_{21}: J3.36, U10.15 (Q4)
/A_{22}: J3.33, U10.14 (Q5)
/A_{23}: J3.32, U10.13 (Q6)
/BRP: U1.21 (BRP), U2.65 (BRP)
/CDC: U1.5 (CDC), U2.79 (CDC)
/CDCD_{0}: U1.17 (D_{0}), U2.68 (CDCD_{0})
/CDCD_{1}: U1.19 (D_{1}), U2.69 (CDCD_{1})
/CDCD_{2}: U1.16 (D_{2}), U2.70 (CDCD_{2})
/CDCD_{3}: U1.14 (D_{3}), U2.73 (CDCD_{3})
/CDCD_{4}: U1.11 (D_{4}), U2.74 (CDCD_{4})
/CDCD_{5}: U1.12 (D_{5}), U2.75 (CDCD_{5})
/CDCD_{6}: U1.9 (D_{6}), U2.76 (CDCD_{6})
/CDCD_{7}: U1.8 (D_{7}), U2.77 (CDCD_{7})
/CDCE: U1.4 (EN), U2.80 (CDCE), Y1.1 (EN)
/CK16: U1.43 (CLK), Y1.5 (OUT)
/DCK: U1.6 (DCK), U2.83 (CLK)
/DIR: U3.16 (Q0), U6.6 (A4), U14.3
/DRS: U3.10 (Q2), U6.8 (A6), U14.1
/D_{0}: J3.29, U2.12 (D_{0}), U9.2 (D0), U9.19 (Q0), U11.2 (D0)
/D_{1}: J3.30, U2.15 (D_{1}), U9.3 (D1), U9.18 (Q1), U11.3 (D1)
/D_{2}: J3.27, U2.16 (D_{2}), U9.4 (D2), U9.17 (Q2), U11.4 (D2)
/D_{3}: J3.25, U2.17 (D_{3}), U9.5 (D3), U9.16 (Q3), U11.5 (D3)
/D_{4}: J3.26, U2.18 (D_{4}), U9.6 (D4), U9.15 (Q4), U11.6 (D4)
/D_{5}: J3.23, U2.20 (D_{5}), U9.7 (D5), U9.14 (Q5), U11.7 (D5)
/D_{6}: J3.24, U2.21 (D_{6}), U9.8 (D6), U9.13 (Q6), U11.8 (D6)
/D_{7}: J3.21, U2.22 (D_{7}), U9.9 (D7), U9.12 (Q7), U11.9 (D7)
/D_{8}: J3.19, U2.63 (D_{8}), U6.18 (Y0), U7.2 (D0), U7.19 (Q0), U8.2 (D0), U8.19 (Q0), U10.2 (D0)
/D_{9}: J3.20, U2.61 (D_{9}), U6.17 (Y1), U7.3 (D1), U7.18 (Q1), U8.3 (D1), U8.18 (Q1), U10.3 (D1)
/D_{10}: J3.17, U2.60 (D_{10}), U6.16 (Y2), U7.4 (D2), U7.17 (Q2), U8.4 (D2), U8.17 (Q2), U10.4 (D2)
/D_{11}: J3.18, U2.58 (D_{11}), U6.15 (Y3), U7.5 (D3), U7.16 (Q3), U8.5 (D3), U8.16 (Q3), U10.5 (D3)
/D_{12}: J3.15, U2.57 (D_{12}), U3.2 (D0), U6.14 (Y4), U7.6 (D4), U7.15 (Q4), U8.6 (D4), U8.15 (Q4), U10.6 (D4)
/D_{13}: J3.13, U2.56 (D_{13}), U3.3 (D1), U6.13 (Y5), U7.7 (D5), U7.14 (Q5), U8.7 (D5), U8.14 (Q5), U10.7 (D5)
/D_{14}: J3.14, U2.55 (D_{14}), U3.6 (D2), U6.12 (Y6), U7.8 (D6), U7.13 (Q6), U8.8 (D6), U8.13 (Q6), U10.8 (D6)
/D_{15}: J3.11, U2.54 (D_{15}), U3.7 (D3), U6.11 (Y7), U7.9 (D7), U7.12 (Q7), U8.9 (D7), U8.12 (Q7)
/RD: U1.24 (RD), U13.6
/SIDE: U3.15 (Q1), U6.7 (A5), U14.9
/STEP: U2.31 (STP), U14.5
/WG: U1.26 (WG), U14.11
/WP: U2.25 (WP), U6.3 (A1), U13.4
/WPC: U1.31 (WPC), U3.9 (Q3), U6.9 (A7)
/WR: U1.28 (WR), U14.13
/WRP: U1.27 (WRP), U2.64 (WRP)
/~ASH: U4.5 (O1), U5.2
/~AS: U2.5 (AS), U7.1 (OE)
/~BG: J2.20, U2.33 (BG)
/~BR: J2.19, U2.34 (BR)
/~BUSY: U2.81 (BSY), U6.5 (A3)
/~CRCSH: U4.7 (O3), U13.9
/~CRCS: U2.8 (CRCS), U13.1
/~CS: U2.4 (CS), U4.4 (O0), U5.11, U6.1 (G1)
/~DA: J2.24, U2.36 (DA)
/~DCHG: J1.34, RN1.5 (R4.2), U6.4 (A2)
/~DIR: J1.18, U14.4
/~DRS/~MON: J1.12, J1.16, U14.2
/~DS: U2.6 (DS), U10.1 (OE), U11.1 (OE)
/~EA: J2.26, U2.37 (EA)
/~IOS: J3.12, U12.1 (G)
/~LS: J3.6, R3.1, U2.39 (LS)
/~MAS: U4.6 (O2), U5.5
/~RD: J1.30, RN1.4 (R3.2), U13.5
/~RES: J2.13, U1.1 (MR), U2.1 (MR)
/~RE: J3.8, U6.19 (G2)
/~SIDE: J1.32, U14.8
/~STEP: J1.20, U14.6
/~TR0: J1.26, RN1.2 (R1.2), U6.2 (A0)
/~UA: J2.23, U2.35 (UA)
/~US: J3.5, R2.1, U2.40 (US)
/~WE: J3.7, U2.41 (WE), U4.14 (A0), U5.3, U5.6, U5.12
/~WG: J1.24, U14.10
/~WP: J1.28, RN1.3 (R2.2), U13.3
/~WR: J1.22, U14.12
GND: C2.2, C3.2, C4.2, C5.2, C6.2, C7.2, C8.2, C9.2, C10.2, C11.2, C12.2, C13.2, C14.2, C15.2, C16.2, C17.2, C19.2, C20.2, C21.2, C22.2, J1.7, J1.9, J1.11, J1.13, J1.15, J1.17, J1.19, J1.21, J1.23, J1.25, J1.27, J1.29, J1.31, J1.33, J2.4, J2.10, J2.16, J2.21, J2.22, J2.28, J3.4, J3.10, J3.22, J3.40, J3.52, M1.1, R1.1, U1.10 (GND), U1.22 (GND), U1.30 (GND), U1.42 (GND), U2.7 (GND), U2.19 (GND), U2.32 (GND), U2.42 (GND), U2.47 (GND), U2.59 (GND), U2.72 (GND), U2.82 (GND), U3.12 (GND), U4.8 (GND), U4.13 (A1), U5.7 (GND), U6.10 (GND), U7.10 (GND), U8.10 (GND), U9.10 (GND), U10.10 (GND), U11.10 (GND), U12.3 (R0), U12.5 (R1), U12.9 (R3), U12.10 (GND), U12.12 (R4), U12.13 (P5), U12.14 (R5), U12.15 (P6), U12.16 (R6), U12.17 (P7), U12.18 (R7), U13.7 (GND), U14.7 (GND), Y1.4 (GND)
unnamed: C1.1, U5.13
unnamed: C20.1, C22.1, R5.1, U13.11
unnamed: C21.1, R6.1, U13.13
unnamed: U2.29 (STPBK), U13.10
unnamed: R5.2, R6.2, U2.28 (STPJ)
unnamed: U2.30 (STPK), U13.12
unnamed: C1.2, R1.2, U3.4 (E23), U3.13 (E01)
unnamed: U4.15 (E), U5.10
unnamed: C18.1, U4.12 (O0)
unnamed: U4.11 (O1), U8.1 (OE), U9.1 (OE)
unnamed: U5.1, U7.11 (Cp)
unnamed: C18.2, R4.1, U8.11 (Cp), U9.11 (Cp)
unnamed: U5.4, U10.11 (Cp), U11.11 (Cp)
unnamed: U4.1 (E), U12.19 (P=R)
unnamed: U5.8, U13.2
unnamed: U5.9, U13.8

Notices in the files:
floppy/floppy.kicad_pcb:
Copyright © 2026
